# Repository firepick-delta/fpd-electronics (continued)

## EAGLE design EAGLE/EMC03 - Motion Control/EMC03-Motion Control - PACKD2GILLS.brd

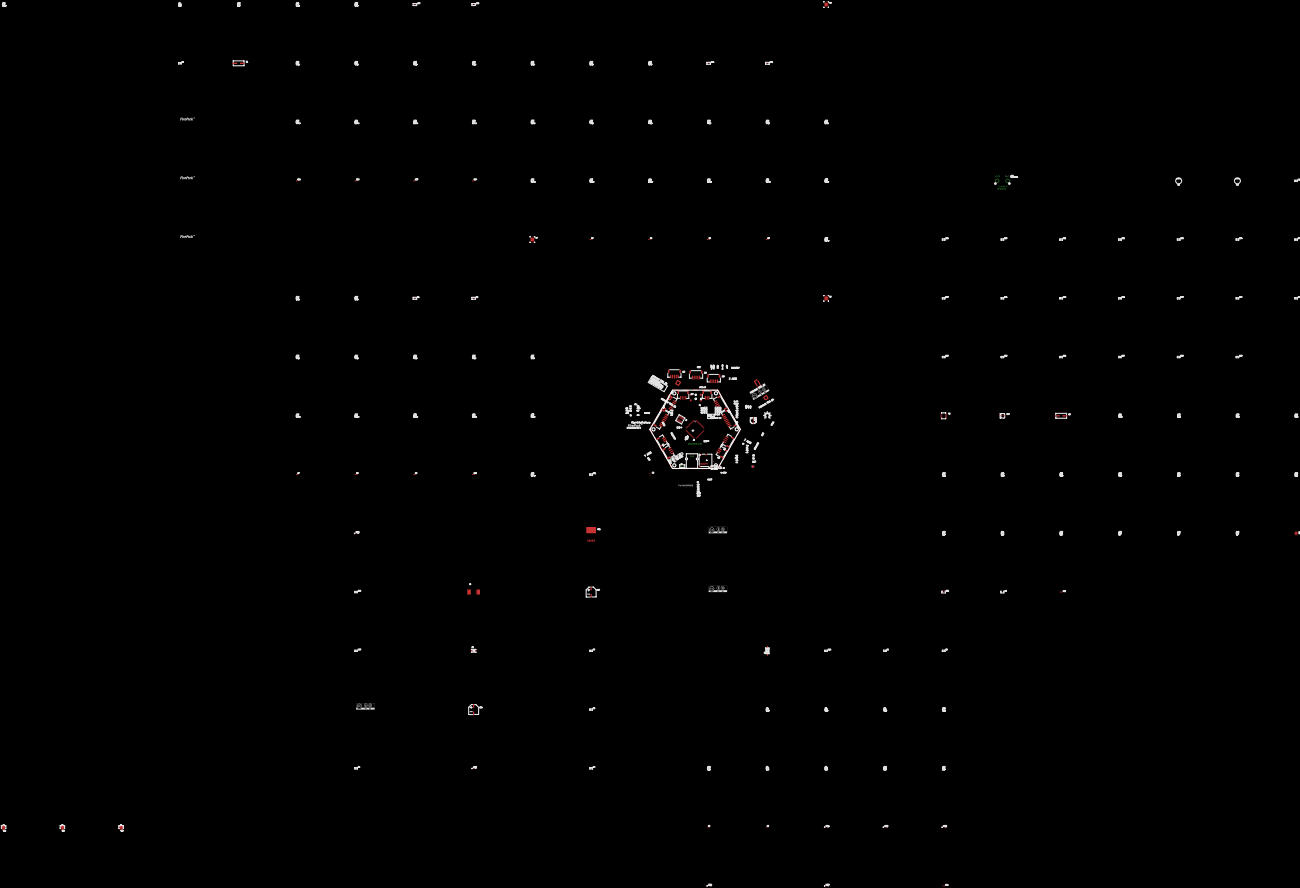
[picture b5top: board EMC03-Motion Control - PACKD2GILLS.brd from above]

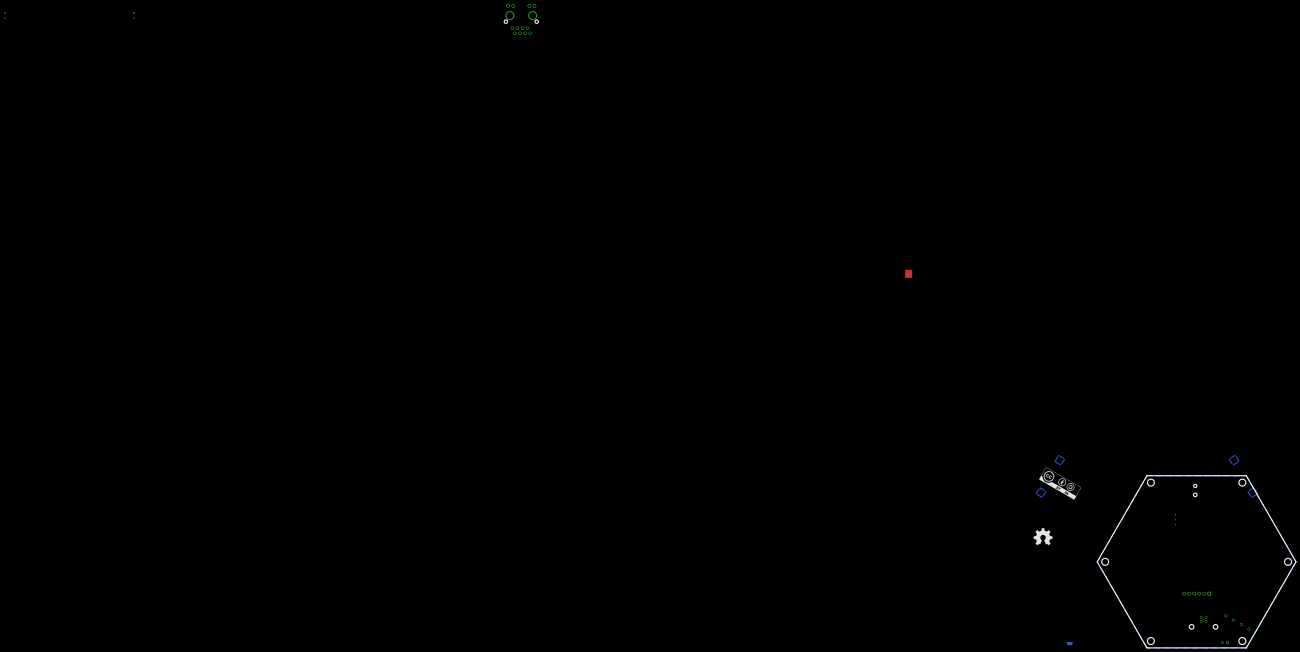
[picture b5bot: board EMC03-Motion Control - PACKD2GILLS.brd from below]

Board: 4 copper layers, 100.0 x 86.6 mm, 209 parts (3 on the bottom side), 116 nets.

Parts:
C1, C11, C12, C75: 12pF; C0603
C2, C4, C5, C7, C9, C13, C18, C19, C23, C24, C25, C28, C29, C34: 0.1uF; C0603
C3: 100uF; PANASONIC_D
C6, C8, C10, C27: 10nF; C0603
C14, C22: 10uF; C-RAD-6.3MM
C15, C17, C39, C41, C42, C51, C52, C61, C62, C64, C65, C74: 100 nF; C0603
C16, C40, C63: 470 nF; C0603
C20: 1uF; C-SMD-4MM
C21, C43, C44, C45, C46, C53, C54, C55, C56, C66, C67, C68, C69: 470pF; C0603
C26, C30, C31, C32: 18pF; C0603
C33, C35, C36: 1uF; C0603
C37: 220uF; C-SMD-10MM
C38: 470uF; C-SMD-10MM
C47, C48, C57, C58, C70, C71: 100nF; C0603
C49, C59, C72: 22 nF; C0603
C50, C60, C73: 0.33uF; C0603
C76: 0.47uF; C0603
D1: 1N4148; SOD-123
D2: SJPB-H6; DIO-SM2
D3, D4, D5, D6, D7, D8, D9, D10, D11, D12, D13, D14: MSS1P6; MICRO-SMP
FB1, FB2: BLM18AG121SN1D; F0603
FID1, FID2, FID3, FID4, FID5, FID6, FID7: FIDUCIAL
J1: UART0; CON-HDR-6POS-MALE
J2: FTSH-105-1-L-DV; FTSH-105-01-XXX-DV-K
J3: USB-B; USB-B(THRU)
J4: MicroSD; MICRO-SD-SOCKET-PP
J5, J6, J7: S3B-PH-SM4; CONN-JST-PH-2.0MM-3P-SMT-RA
J8: 694106106102; PJ-694106106102
J9: S2B-PH-SM4; CON-HDR-2POS-MALE
J10, J11, J12: S4B-PH-SM4; CONN-JST-PH-2.0MM-4P-SMT-RA
J13, J14, J15: S5B-PH-SM4; CONN-JST-PH-2.0MM-5P-SMT-RA
J16, J17: S8B-PH-SM4; CONN-JST-PH-2.0MM-8P-SMT-RA
J18, J19: S6B-PH-SM4; CONN-JST-PH-2.0MM-6P-SMT-RA
L1: 100uH; L-SMD-12.5MM
LED1, LED2, LED3, LED4: GREEN; LED0603
LED5, LED6, LED7: RED; LED0603
LOGO1, LOGO4, LOGO10, LOGO11, LOGO12: LOGO-FIREPICKLARGE; LOGO-FIREPICK
LOGO2, LOGO5: LOGO-OSHWMEDIUM; LOGO-OSHW-MEDIUM
LOGO3, LOGO6, LOGO7, LOGO8, LOGO9: LOGO-CC-BY-SALARGE; LOGO-CC-BY-SA
Q1: 12MHz; HC-49/U-S
Q2: 25MHz; HC-49/U-S
R1, R2, R44, R45, R46, R47: 0.22; R1206
R3, R13: 1M; R0603
R4, R5, R18, R36: 10k; R0603
R6, R7, R8, R9, R41: 470R; R0603
R10, R11, R12, R15: 22R; R0603
R14: 12.1K; R0603
R16: 1.5K; R0603
R17, R23, R24, R25, R26, R28, R35, R37, R43: 10K; R0603
R19, R20, R21: 20K; R0603
R22, R30, R31, R32: 49R9; R0603
R27: 100K; R0603
R29: 4.7K; R0603
R33, R34: 330R; R0603
R38, R39: 1K; R0603
R40: 100R; R0603
R42: 1.2K; R0603
RJ1: HR911105A; MAGJACK(HR911105A)
S1: SWS001; SMS-001
S2, S3: 147873-2; 0603
TP1: +3.3V; CON-TESTPOINT
TP2: +5V; CON-TESTPOINT
TP3: +24V; CON-TESTPOINT
TP4: GND; CON-TESTPOINT
U1: LPC1768; LQFP-100
U2: SP3485; SOICN-8
U3: LAN8720A; QFN-24
U4: 74LVC1G04W5-7; SOT-25
U5: 74AHCT; SC70
U6, U7, U8: TMC2130-LA; QFN36-(5X6)
U$25: TIN-WHISKERSTSTOP; TIN-WHISKERS-TSTOP
VR1: TC1015-3.3VCT713; SOT-23-5
VR2: SI-8050JD; TO263-5
VR3, VR4, VR5: KA78L05AMTF; SOT-89

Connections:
1A_1: C45.1, D5.NEG, J10.3, U6.32
1A_2: C68.1, D13.NEG, J11.3, U7.32
1A_3: C55.1, D9.NEG, J12.3, U8.32
1B_1: C46.1, D6.NEG, J10.4, U6.34
1B_2: C69.1, D14.NEG, J11.4, U7.34
1B_3: C56.1, D10.NEG, J12.4, U8.34
2A_1: C44.1, D4.NEG, J10.2, U6.13
2A_2: C67.1, D12.NEG, J11.2, U7.13
2A_3: C54.1, D8.NEG, J12.2, U8.13
2B_1: C43.1, D3.NEG, J10.1, U6.15
2B_2: C66.1, D11.NEG, J11.1, U7.15
2B_3: C53.1, D7.NEG, J12.1, U8.15
!ENABLE: J16.2, J17.2, J18.2, J19.2, R28.1, U5.4, U6.22, U7.22, U8.22
!ENABLE_BUF: U1.38, U5.2
+3V3: C2.1, C5.2, C6.2, C7.2, C8.2, C9.2, C10.2, C13.2, C22.POS, C23.2, C33.2, C34.2, C36.2, FB1.1, FB2.2, J1.3, J2.1, J4.4, R4.2, R5.2, R16.2, R17.2, R18.2, R27.2, R28.2, R35.1, R36.1, R37.1, R38.2, R41.2, TP1.1, U1.19, U1.28, U1.42, U1.54, U1.71, U1.84, U1.96, U2.8, U3.9, U4.5, U5.5, VR1.5
+5V: C3.+, C4.1, C38.POS, J5.2, J6.2, J7.2, J13.1, J14.1, J15.1, J16.6, J17.6, J18.6, J19.6, L1.P$2, R42.2, TP2.1, VR2.4
+24V: C15.2, C16.2, C17.1, C37.POS, C39.2, C40.2, C41.1, C42.1, C50.2, C52.1, C60.2, C62.2, C63.2, C64.1, C65.1, C73.2, J8.2, J16.1, J17.1, J18.1, J19.1, R43.2, TP3.1, U6.16, U6.30, U6.31, U7.16, U7.30, U7.31, U8.16, U8.30, U8.31, VR2.1, VR3.1, VR4.1, VR5.1
A: J16.4, J17.4, J18.4, J19.4, R39.2, R40.1, U2.6
B: J16.5, J17.5, J18.5, J19.5, R38.1, R40.2, U2.7
BRA: C48.1, D3.POS, D4.POS, R44.2, U6.33
BRA2: C71.1, D11.POS, D12.POS, R46.2, U7.33
BRA3: C58.1, D7.POS, D8.POS, R1.2, U8.33
BRB: C47.1, D5.POS, D6.POS, R45.2, U6.14
BRB2: C70.1, D13.POS, D14.POS, R47.2, U7.14
BRB3: C57.1, D9.POS, D10.POS, R2.2, U8.14
CLK: U6.1, U7.1, U8.1
CPI: C49.2, U6.28
CPI1: C59.2, U8.28
CPI2: C72.2, U7.28
CPO: C49.1, U6.27
CPO1: C59.1, U8.27
CPO2: C72.1, U7.27
CRSPIN: R12.2, U3.11
DFU: R5.1, S3.2, U1.49
DI: U1.62, U2.4
DPWR: C27.2, C28.2, FB2.1, U1.10, U1.12
DTR: C29.1, J1.6
DTR1: U1.58, U2.2, U2.3
ESTOP: D1.C, U1.39
ESTOP_OE: D1.A, J9.2, R27.1, U5.1
ETH_CRS_DV: R12.1, U1.92
ETH_MDC: U1.87, U3.13
ETH_MDIO: R16.1, U1.86, U3.12
ETH_REF_CLK: R15.1, U1.88
ETH_RXD0: R10.1, U1.91
ETH_RXD1: R11.1, U1.90
ETH_RX_ER: R17.1, U1.89, U3.10
ETH_TXD0: U1.95, U3.17
ETH_TXD1: U1.94, U3.18
ETH_TX_EN: U1.93, U3.16
GND: C1.1, C2.2, C3.-, C4.2, C5.1, C6.1, C7.1, C8.1, C9.1, C10.1, C11.1, C12.1, C13.1, C14.NEG, C16.1, C17.2, C18.1, C19.1, C20.NEG, C21.1, C22.NEG, C23.1, C24.1, C25.1, C26.1, C27.1, C28.1, C30.1, C31.1, C32.1, C33.1, C34.1, C35.1, C36.1, C37.NEG, C38.NEG, C40.1, C41.2, C42.2, C43.2, C44.2, C45.2, C46.2, C47.2, C48.2, C50.1, C51.1, C52.2, C53.2, C54.2, C55.2, C56.2, C57.2, C58.2, C60.1, C61.1, C63.1, C64.2, C65.2, C66.2, C67.2, C68.2, C69.2, C70.2, C71.2, C73.1, C74.1, C75.1, C76.1, D2.NEG, J2.3, J2.5, J2.9, J3.4, J4.6, J4.CD2, J4.GND1, J5.3, J6.3, J7.3, J13.5, J14.5, J15.5, J16.3, J17.3, J18.3, J19.3, LED1.C, LED2.C, LED3.C, LED4.C, LED5.C, LED6.C, LED7.C, R1.1, R2.1, R14.1, R19.1, R20.1, R21.1, R23.1, R29.1, R33.2, R34.2, R39.1, R44.1, R45.1, R46.1, R47.1, RJ1.SHLD0, RJ1.SHLD1, S1.1, S2.1, S3.1, TP4.1, U1.11, U1.15, U1.31, U1.41, U1.55, U1.72, U1.83, U1.97, U2.5, U3.PAD, U4.3, U5.3, U6.12, U6.18, U6.24, U6.35, U6.36, U6.PAD, U7.12, U7.18, U7.24, U7.35, U7.36, U7.PAD, U8.12, U8.18, U8.24, U8.35, U8.36, U8.PAD, VR2.3, VR2.GND, VR3.2, VR4.2, VR5.2
ISP_COM: R4.1, S2.2, U1.48
LED1/REGOFF: RJ1.9, U3.3
LED2/NINTSEL: R23.2, RJ1.12, U3.2
MISO: J4.7, R36.2, U1.77, U6.5, U7.5, U8.5
MOSI: J4.3, R35.2, U1.76, U6.4, U7.4, U8.4
unnamed: R15.2, U4.4
unnamed: C76.2, VR2.5
unnamed: J9.1, R29.2
unnamed: C14.POS, C18.2, C19.2, C24.2, C25.2, FB1.2, R22.2, R30.2, R31.2, R32.2, RJ1.4, RJ1.5, U3.1, U3.19
unnamed: R33.1, RJ1.11
unnamed: R34.1, RJ1.10
unnamed: LED5.A, R41.1
unnamed: LED7.A, R42.1
unnamed: LED6.A, R43.1
unnamed: D2.POS, L1.P$1, VR2.2
unnamed: C35.2, VR1.2
unnamed: LED1.A, R6.1
unnamed: C20.POS, C21.2, U3.6
unnamed: LED2.A, R7.1
unnamed: LED4.A, R9.1
unnamed: LED3.A, R8.1
NINT/REFCLK0: U3.14, U4.2
RBIAS: R14.2, U3.24
RD+: C31.2, R31.1, RJ1.3, U3.23
RD-: C32.2, R32.1, RJ1.6, U3.22
RESET: C29.2, R18.1, S1.2, U1.17
RESET_N: J2.10, U1.4
RO: U1.63, U2.1
RTCK: J2.7, U1.100
RXD0PIN: R10.2, U3.8
RXD1PIN: R11.2, U3.7
SCK: J4.5, U1.78, U6.3, U7.3, U8.3
SD_CS: J4.2, R37.2, U1.79
SPI_!CS1: U1.9, U6.2
SPI_!CS2: U1.8, U7.2
SPI_!CS3: U1.7, U8.2
STAT_LED4: R6.2, U1.37
STAT_LED5: R7.2, U1.36
STAT_LED6: R8.2, U1.35
STAT_LED7: R9.2, U1.34
SWDCLK: J2.4, U1.5
SWDIO: J2.2, U1.3
SWO: J2.6, U1.1
TD+: C26.2, R22.1, RJ1.1, U3.21
TD-: C30.2, R30.1, RJ1.2, U3.20
TDI: J2.8, U1.2
USB_D+: J3.3, U1.29
USB_D-: J3.2, U1.30
VCC1: C51.2, U6.8, U6.26, VR3.3
VCC2: C74.2, U7.8, U7.26, VR4.3
VCC3: C61.2, U8.8, U8.26, VR5.3
VCP: C39.1, U6.29
VCP1: C15.1, U8.29
VCP2: C62.1, U7.29
VR_IN: J3.1, VR1.1, VR1.3
XTAL1: C1.2, Q1.1, R3.1, U1.22
XTAL2: C75.2, Q1.2, R3.2, U1.23
XTAL3: C11.2, Q2.1, R13.1, U3.5
XTAL4: C12.2, Q2.2, R13.2, U3.4
X_MIN: R19.2, R26.1, U1.40
X_STOP: J5.1, R26.2
Y_MIN: R20.2, R25.1, U1.43
Y_STOP: J6.1, R25.2
Z_MIN: R21.2, R24.1, U1.44
Z_STOP: J7.1, R24.2

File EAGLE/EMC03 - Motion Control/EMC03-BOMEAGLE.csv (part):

Part;Value;Device;Package;Description;BOM;DNP;PARTNO
C1;12pF;CPL-CAP-C0G-0603-12PF-50V;C0603;"Capacitor: 12pF, 50V, 5%;";;;
C2;0.1u;CAP0805;0805;Capacitor;;;CC0805ZRY5V9BB104
C3;100uF;CPOL-USD;PANASONIC_D;POLARIZED CAPACITOR, American symbol;;;25TXV100M6.3X8
C4;0.1u;CAP0805;0805;Capacitor;;;CC0805ZRY5V9BB104
C5;0.1uF;CPL-CAP-X5R-0603-0.1UF-35V;C0603;"Capacitor: 0.1uF, 35V, 10%, X5R;";;;
C6;10nF;CPL-CAP-X7R-10NF-16V;C0603;"Capacitor: 10nF(0.01uF), 16V, 5%;";;;
C7;0.1uF;CPL-CAP-X5R-0603-0.1UF-35V;C0603;"Capacitor: 0.1uF, 35V, 10%, X5R;";;;
C8;10nF;CPL-CAP-X7R-10NF-16V;C0603;"Capacitor: 10nF(0.01uF), 16V, 5%;";;;
C9;0.1uF;CPL-CAP-X5R-0603-0.1UF-35V;C0603;"Capacitor: 0.1uF, 35V, 10%, X5R;";;;
C10;10nF;CPL-CAP-X7R-10NF-16V;C0603;"Capacitor: 10nF(0.01uF), 16V, 5%;";;;
C11;12pF;CPL-CAP-C0G-0603-12PF-50V;C0603;"Capacitor: 12pF, 50V, 5%;";;;
C12;12pF;CPL-CAP-C0G-0603-12PF-50V;C0603;"Capacitor: 12pF, 50V, 5%;";;;
C13;0.1uF;CPL-CAP-X5R-0603-0.1UF-35V;C0603;"Capacitor: 0.1uF, 35V, 10%, X5R;";;;
C14;10uF;CPL-CAP-ALU-RAD-10UF-50V;C-RAD-6.3MM;;;;
C15;100 nF;CPL-CAP-X7R-0603-100NF-50V;C0603;"Capacitor: 100nF, 50V, 10%;";;;
C16;470 nF;CPL-CAP-X7R-0603-0.47UF-35V;C0603;;;;
C17;100 nF;CPL-CAP-X7R-0603-100NF-50V;C0603;"Capacitor: 100nF, 50V, 10%;";;;
C18;0.1uF;CPL-CAP-X7R-0603-0.1UF-35V;C0603;"Capacitor: 0.1uF, 35V, 10%, X7R;";;;
C19;0.1uF;CPL-CAP-X7R-0603-0.1UF-35V;C0603;"Capacitor: 0.1uF, 35V, 10%, X7R;";;;
C20;1uF;CPL-CAP-ALU-SMD-1UF-50V;C-SMD-4MM;"Capacitor, Al-Electrolytic: 1uF,  50v, 20%;";;;
C21;470pF;CPL-CAP-X7R-0603-470PF-100V;C0603;"Capacitor: 470pF, 100V, 5%;";;;
C22;10uF;CPL-CAP-ALU-RAD-10UF-50V;C-RAD-6.3MM;;;;
C23;0.1uF;CPL-CAP-X7R-0603-0.1UF-35V;C0603;"Capacitor: 0.1uF, 35V, 10%, X7R;";;;
C24;0.1uF;CPL-CAP-X7R-0603-0.1UF-35V;C0603;"Capacitor: 0.1uF, 35V, 10%, X7R;";;;
C25;0.1uF;CPL-CAP-X7R-0603-0.1UF-35V;C0603;"Capacitor: 0.1uF, 35V, 10%, X7R;";;;
C26;18pF;CPL-CAP-C0G-0603-18PF-50V;C0603;"Capacitor: 18pF, 50V, 5%;";;;
C27;10nF;CPL-CAP-X7R-10NF-16V;C0603;"Capacitor: 10nF(0.01uF), 16V, 5%;";;;
C28;0.1uF;CPL-CAP-X5R-0603-0.1UF-35V;C0603;"Capacitor: 0.1uF, 35V, 10%, X5R;";;;
C29;0.1uF;CPL-CAP-X7R-0603-0.1UF-35V;C0603;"Capacitor: 0.1uF, 35V, 10%, X7R;";;;
C30;18pF;CPL-CAP-C0G-0603-18PF-50V;C0603;"Capacitor: 18pF, 50V, 5%;";;;
C31;18pF;CPL-CAP-C0G-0603-18PF-50V;C0603;"Capacitor: 18pF, 50V, 5%;";;;
C32;18pF;CPL-CAP-C0G-0603-18PF-50V;C0603;"Capacitor: 18pF, 50V, 5%;";;;
C33;1uF;CPL-CAP-X5R-0603-1UF-50V;C0603;"Capacitor: 0.1uF, 50V, 10%;";;;
C34;0.1uF;CPL-CAP-X5R-0603-0.1UF-35V;C0603;"Capacitor: 0.1uF, 35V, 10%, X5R;";;;
C35;1uF;CPL-CAP-X5R-0603-1UF-50V;C0603;"Capacitor: 0.1uF, 50V, 10%;";;;
C36;1uF;CPL-CAP-X5R-0603-1UF-50V;C0603;"Capacitor: 0.1uF, 50V, 10%;";;;
C37;220uF;CPL-CAP-ALU-SMD-220-50V;C-SMD-10MM;"Capacitor: Al-Electrolytic, 220uF, 50V;";;;
C38;470uF;CPL-CAP-ALU-SMD-470UF-25V;C-SMD-10MM;"Capacitor: Al-Electrolytic, 470uF, 25V;";;;
C39;100 nF;CPL-CAP-X7R-0603-100NF-50V;C0603;"Capacitor: 100nF, 50V, 10%;";;;
C40;470 nF;CPL-CAP-X7R-0603-0.47UF-35V;C0603;;;;
C41;100 nF;CPL-CAP-X7R-0603-100NF-50V;C0603;"Capacitor: 100nF, 50V, 10%;";;;
C42;100 nF;CPL-CAP-X7R-0603-100NF-50V;C0603;"Capacitor: 100nF, 50V, 10%;";;;
C43;470pF;CPL-CAP-X7R-0603-470PF-100V;C0603;"Capacitor: 470pF, 100V, 5%;";;;
C44;470pF;CPL-CAP-X7R-0603-470PF-100V;C0603;"Capacitor: 470pF, 100V, 5%;";;;
C45;470pF;CPL-CAP-X7R-0603-470PF-100V;C0603;"Capacitor: 470pF, 100V, 5%;";;;
C46;470pF;CPL-CAP-X7R-0603-470PF-100V;C0603;"Capacitor: 470pF, 100V, 5%;";;;
C47;100nF;CPL-CAP-X7R-0603-100NF-50V;C0603;"Capacitor: 100nF, 50V, 10%;";;;
C48;100nF;CPL-CAP-X7R-0603-100NF-50V;C0603;"Capacitor: 100nF, 50V, 10%;";;;
C49;22 nF;"CPL-CAP-X7R-0603-22NF-50V"";C0603""";;Capacitor: 22nF, 50V, 10%,;;;
C50;0.33uF;CPL-CAP-X7R-0603-0.33UF-35V;C0603;"Capacitor: 0.33uF, 35V, 10%, X7R;";;;
"
C51";100 nF;CPL-CAP-X7R-0603-100NF-50V;C0603;"Capacitor: 100nF, 50V, 10%;";;;
C52;100 nF;CPL-CAP-X7R-0603-100NF-50V;C0603;"Capacitor: 100nF, 50V, 10%;";;;
C53;470pF;CPL-CAP-X7R-0603-470PF-100V;C0603;"Capacitor: 470pF, 100V, 5%;";;;
C54;470pF;CPL-CAP-X7R-0603-470PF-100V;C0603;"Capacitor: 470pF, 100V, 5%;";;;
C55;470pF;CPL-CAP-X7R-0603-470PF-100V;C0603;"Capacitor: 470pF, 100V, 5%;";;;
C56;470pF;CPL-CAP-X7R-0603-470PF-100V;C0603;"Capacitor: 470pF, 100V, 5%;";;;
C57;100nF;CPL-CAP-X7R-0603-100NF-50V;C0603;"Capacitor: 100nF, 50V, 10%;";;;
C58;100nF;CPL-CAP-X7R-0603-100NF-50V;C0603;"Capacitor: 100nF, 50V, 10%;";;;
C59;22 nF;"CPL-CAP-X7R-0603-22NF-50V"";C0603""";;Capacitor: 22nF, 50V, 10%,;;;
C60;0.33uF;CPL-CAP-X7R-0603-0.33UF-35V;C0603;"Capacitor: 0.33uF, 35V, 10%, X7R;";;;
C61;100 nF;CPL-CAP-X7R-0603-100NF-50V;C0603;"Capacitor: 100nF, 50V, 10%;";;;
C62;100 nF;CPL-CAP-X7R-0603-100NF-50V;C0603;"Capacitor: 100nF, 50V, 10%;";;;
C63;470 nF;CPL-CAP-X7R-0603-0.47UF-35V;C0603;;;;
C64;100 nF;CPL-CAP-X7R-0603-100NF-50V;C0603;"Capacitor: 100nF, 50V, 10%;";;;
C65;100 nF;CPL-CAP-X7R-0603-100NF-50V;C0603;"Capacitor: 100nF, 50V, 10%;";;;
C66;470pF;CPL-CAP-X7R-0603-470PF-100V;C0603;"Capacitor: 470pF, 100V, 5%;";;;
C67;470pF;CPL-CAP-X7R-0603-470PF-100V;C0603;"Capacitor: 470pF, 100V, 5%;";;;
C68;470pF;CPL-CAP-X7R-0603-470PF-100V;C0603;"Capacitor: 470pF, 100V, 5%;";;;
C69;470pF;CPL-CAP-X7R-0603-470PF-100V;C0603;"Capacitor: 470pF, 100V, 5%;";;;
C70;100nF;CPL-CAP-X7R-0603-100NF-50V;C0603;"Capacitor: 100nF, 50V, 10%;";;;
C71;100nF;CPL-CAP-X7R-0603-100NF-50V;C0603;"Capacitor: 100nF, 50V, 10%;";;;
C72;22 nF;"CPL-CAP-X7R-0603-22NF-50V"";C0603""";Capacitor Specs: 22nF, 50V, 10%,;;;;
C73;0.33uF;CPL-CAP-X7R-0603-0.33UF-35V;C0603;"Capacitor: 0.33uF, 35V, 10%, X7R;";;;
C74;100 nF;CPL-CAP-X7R-0603-100NF-50V;C0603;"Capacitor: 100nF, 50V, 10%;";;;
C75;12pF;CPL-CAP-C0G-0603-12PF-50V;C0603;"Capacitor: 12pF, 50V, 5%;";;;
D1;1N4148;DIODESOD123;SOD-123;Diode;;;1N4148W-7-F
D2;SJPB-H6;CPL-DIO-SJPB-H6-SM2;DIO-SM2;Diode: Rectifier, Schottky, 40V;;;
D3;MSS1P6;CPL-DIO-MSS1P6-MICROSMP;MICRO-SMP;"Diode: Rectifier, 1A, 60V;";;;
D4;MSS1P6;CPL-DIO-MSS1P6-MICROSMP;MICRO-SMP;"Diode: Rectifier, 1A, 60V;";;;
D5;MSS1P6;CPL-DIO-MSS1P6-MICROSMP;MICRO-SMP;"Diode: Rectifier, 1A, 60V;";;;
D6;MSS1P6;CPL-DIO-MSS1P6-MICROSMP;MICRO-SMP;"Diode: Rectifier, 1A, 60V;";;;
D7;MSS1P6;CPL-DIO-MSS1P6-MICROSMP;MICRO-SMP;"Diode: Rectifier, 1A, 60V;";;;
D8;MSS1P6;CPL-DIO-MSS1P6-MICROSMP;MICRO-SMP;"Diode: Rectifier, 1A, 60V;";;;
D9;MSS1P6;CPL-DIO-MSS1P6-MICROSMP;MICRO-SMP;"Diode: Rectifier, 1A, 60V;";;;
D10;MSS1P6;CPL-DIO-MSS1P6-MICROSMP;MICRO-SMP;"Diode: Rectifier, 1A, 60V;";;;
D11;MSS1P6;CPL-DIO-MSS1P6-MICROSMP;MICRO-SMP;"Diode: Rectifier, 1A, 60V;";;;
D12;MSS1P6;CPL-DIO-MSS1P6-MICROSMP;MICRO-SMP;"Diode: Rectifier, 1A, 60V;";;;
D13;MSS1P6;CPL-DIO-MSS1P6-MICROSMP;MICRO-SMP;"Diode: Rectifier, 1A, 60V;";;;
D14;MSS1P6;CPL-DIO-MSS1P6-MICROSMP;MICRO-SMP;"Diode: Rectifier, 1A, 60V;";;;
FB1;BLM15HBK1608H220-T0603;BLM15HBK1608H220-T0603;F0603;EMIFIL (R) Chip Ferrite Bead for GHz Noise;;;
FB2;BK1608H220-T;BLM15HBK1608H220-T0603;F0603;EMIFIL (R) Chip Ferrite Bead for GHz Noise;;;
FID1;FIDUCIAL;FIDUCIAL;FIDUCIAL;;EXCLUDE;;
FID2;FIDUCIAL;FIDUCIAL;FIDUCIAL;;EXCLUDE;;
FID3;FIDUCIAL;FIDUCIAL;FIDUCIAL;;EXCLUDE;;
FID4;FIDUCIAL;FIDUCIAL;FIDUCIAL;;EXCLUDE;;
FID5;FIDUCIAL;FIDUCIAL;FIDUCIAL;;EXCLUDE;;
FID6;FIDUCIAL;FIDUCIAL;FIDUCIAL;;EXCLUDE;;
FID7;FIDUCIAL;FIDUCIAL;FIDUCIAL;;EXCLUDE;;
IC1;74AHCT;CPL-IIC-BUF-74AHCT-SC70;SC70;"Buffer/Line Driver: 74AHCT-Series, Vin=3-5.5V;";;;
J4;8-PIN HDR;CPL-CON-HEADER-0.1IN-8P-M;CON-HDR-8POS-MALE;;;;
J5;8-PIN HDR;CPL-CON-HEADER-0.1IN-8P-M;CON-HDR-8POS-MALE;;;;
J7;CONN-0.1-RA-1X3;MA03-1;MA03-1;PIN HEADER;;;CONN-0.1-RA-1X3
J8;CONN-0.1-RA-1X3;MA03-1;MA03-1;PIN HEADER;;;CONN-0.1-RA-1X3
J9;CONN-0.1-RA-1X3;MA03-1;MA03-1;PIN HEADER;;;CONN-0.1-RA-1X3
J10;UART0;CPL-CON-HEADER-0.1IN-6P-M;CON-HDR-6POS-MALE;"Connector: Header, 0.1-Pitch, 6-Pos, Pins (Male)""";;;
J11;HR911105A;CPL-ETH-MACJACK-LED-SHLD;MAGJACK(HR911105A);"Connector: Ethernet, MagJack, RJ-45, Status LEDs+Shield;";;;
J12;USD-SOCKETSMD;USD-SOCKETSMD;MICRO-SD-SOCKET-PP;microSD Socket;;;
J13;USB-B;CPL-CON-USB-B;USB-B(THRU);Connector: USB, B-type;;;
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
